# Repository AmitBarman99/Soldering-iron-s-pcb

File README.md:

## Soldering Iron

> With special features

1.  OLED temperature display
2.  Increment push button
3.  Decrement push button
4.  USB port for programming
5.  90 degree orientation input-output plug

[click here](./soldering_iron.pdf) to see the Schematic diagram

**The Upper layer of PCB**

**The Lower layer of PCB**

The 3D view of this soldering iron's pcb is here :

<div align="center">
<font size="6">

[3D view](https://grabcad.com/library/soldering-iron-22)

</font>
</div>

> Don't forget to spread the 💝 by giving this repo 🌟

**Thank you**

Credit : **[AMIT BARMAN](https://abhisandhi.netlify.app/)**<br>
        ETC undergrad at **IIESTS**'25

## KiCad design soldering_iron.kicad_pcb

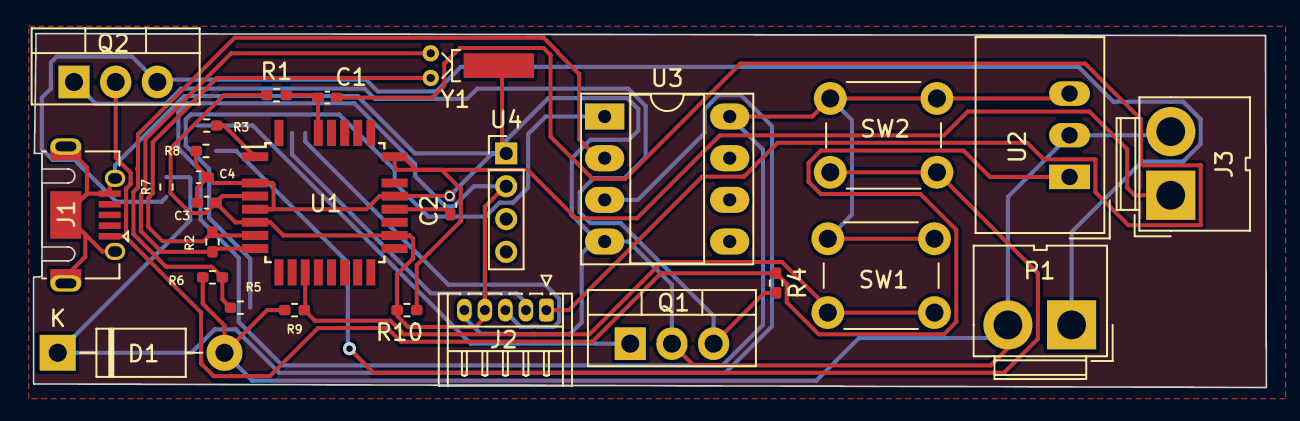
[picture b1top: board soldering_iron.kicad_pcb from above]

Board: 2 copper layers, 75.1 x 21.6 mm, 28 parts (0 on the bottom side), 20 nets.

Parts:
C1, C2, C3: 0.1uF; C_0402_1005Metric_Pad0.74x0.62mm_HandSolder
C4: 2.2nF; C_0402_1005Metric_Pad0.74x0.62mm_HandSolder
D1: 1N5819; D_DO-41_SOD81_P10.16mm_Horizontal
J1: USB_B_Micro; USB_Micro-AB_Molex_47590-0001
J2: PORT; Hirose_DF13-05P-1.25DS_1x05_P1.25mm_Horizontal
J3: VIBRATOR; JWT_A3963_1x02_P3.96mm_Vertical
P1: Plug; JWT_A3963_1x02_P3.96mm_Vertical
Q1: 2SC1945; TO-220-3_Vertical
Q2: IRF4905; TO-220-3_Vertical
R1, R4, R7: 10k; R_0402_1005Metric_Pad0.72x0.64mm_HandSolder
R2: 1M; R_0402_1005Metric_Pad0.72x0.64mm_HandSolder
R3, R6: 1k; R_0402_1005Metric_Pad0.72x0.64mm_HandSolder
R5: 200k; R_0402_1005Metric_Pad0.72x0.64mm_HandSolder
R8, R9: 2K; R_0402_1005Metric_Pad0.72x0.64mm_HandSolder
R10: 10K; R_0402_1005Metric_Pad0.72x0.64mm_HandSolder
SW1, SW2: SW_Push; SW_PUSH_6mm_H5mm
U1: ATmega328P-A; TQFP-32_7x7mm_P0.8mm
U2: TSR_1-2490; Converter_DCDC_TRACO_TSR-1_THT
U3: LM358; DIP-8_W7.62mm_Socket_LongPads
U4: PinHeader_1x04_P2.00mm_Vertical
Y1: Crystal_16MHz; Crystal_DS10_D1.0mm_L4.3mm_Horizontal_1EP_style1

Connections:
+5V: C3.2, J2.4 (VCC_UART), R1.2, R10.2, SW1.1, SW2.1, U1.4 (VCC), U1.6 (VCC), U1.18 (AVCC), U2.3 (Vout), U3.8, U4.2 (VDD)
DTR: C1.1, J2.1 (DTR)
GND: C2.1, C3.1, C4.2, D1.2 (A), J1.5 (GND), J1.6 (Shield), J2.5 (GND_UART), J3.2, P1.2 (AC_N), Q1.2 (E), R6.1, R8.2, R9.2, U1.3 (GND), U1.5 (GND), U1.21 (GND), U2.2 (GND), U3.4, U4.1 (VSS), Y1.3
HALL: J3.1, R10.1, U1.24 (PC1)
L_button: R8.1, SW2.2, U1.2 (PD4)
unnamed: C1.2, R1.1, U1.29 (~RESET/PC6)
unnamed: C2.2, U1.20 (AREF)
unnamed: C4.1, D1.1 (K), R7.2, U3.3 (+)
unnamed: Q1.1 (B), R3.1
unnamed: Q1.3 (C), Q2.1 (G), R4.2
unnamed: R2.1, U1.8 (XTAL2/PB7), Y1.2
unnamed: R2.2, U1.7 (XTAL1/PB6), Y1.1
unnamed: R3.2, U1.1 (PD3)
unnamed: R5.1, U1.23 (PC0), U3.1
unnamed: R5.2, R6.2, U3.2 (-)
RX: J2.3 (RX), U1.30 (PD0)
R_button: R9.1, SW1.2, U1.11 (PD7)
TEMP_sense: P1.1 (AC_P), Q2.3 (S), R7.1
TX: J2.2 (TX), U1.31 (PD1)
VCC: J1.1 (VBUS), Q2.2 (D), R4.1, U2.1 (Vin)

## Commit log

2022-12-25 Designed Schematic
    25/12/2022
2022-12-25 completed annotation
2022-12-25 added schematic pdf file
2022-12-25 completed assignment of footprints
2022-12-27 Designed the whole pcb
2022-12-27 Completed backside layer
2022-12-29 completed frontside layer
2022-12-29 added image
2023-01-02 added 3D viewer file
2023-01-02 converted pdf to png file of upper and lower layer of pcb
2023-01-02 Created readme.md file
2023-01-02 Completed Readme.md
